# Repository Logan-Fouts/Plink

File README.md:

# Plink

**A low-cost, velocity-sensitive USB MIDI keyboard built on the Raspberry Pi Pico, using Hall-effect key switches.**

Plink reads 16 magnetic (Hall-effect) key switches through an analog multiplexer, works out how fast each key was pressed, and sends MIDI notes with velocity over USB. Each key has its own NeoPixel LED, and two front-panel buttons transpose the keyboard up or down.

> **Status:** early prototype (v1.0 hardware in progress). The firmware works on a breadboard build; the PCB and enclosure are still in progress.

---

## Features

- **Velocity-sensitive keys.** Velocity comes from how long a key takes to travel between two points in its stroke, read by an analog Hall sensor.
- **Plug-and-play USB MIDI.** The keyboard shows up as a USB composite device (MIDI + serial). It needs no drivers on Windows, macOS or Linux.
- **Automatic calibration.** Each key's resting value is measured at power-up, and its full-press value is learned as you play.
- **Per-key RGB feedback.** One WS2812 (NeoPixel) LED per key, driven by the RP2040's PIO.
- **Transpose.** ±24 semitones from two push buttons. Press both at once to reset.
- **Unit-tested input logic.** The input logic sits behind a small hardware abstraction layer, so it builds and runs its tests on a desktop machine.

## Hardware

### Bill of materials (v1.0)

| Part | Qty | Notes |
| --- | --- | --- |
| [Raspberry Pi Pico](https://www.raspberrypi.com/products/raspberry-pi-pico/) (RP2040) | 1 | Microcontroller + USB |
| [CD74HC4067](https://www.digikey.com/en/products/detail/texas-instruments/CD74HC4067SM96/390310) 16-channel analog mux | 1 | Feeds all key sensors into a single ADC pin |
| [Hall-effect linear switches](https://www.maxgaming.se/sv/switchar/moyu-studio-yurui-he-linear-switch) | 16 | Magnetic key switches |
| [SS49E linear Hall sensors](https://www.electrokit.com/en/ss49eua-to-92-hall-effektsensor-2mv/g) | 16 | One under each switch |
| [WS2812 NeoPixels](https://www.digikey.com/en/products/detail/adafruit-industries-llc/1655/5154679) | 16 | One per key |
| Momentary push buttons | 2 | Transpose down / up |

### Pinout

All pin assignments live in [`src/config.h`](src/config.h).

### Design files

- [`hardware/plink_kicad/`](hardware/plink_kicad): KiCad schematic, PCB and custom symbol/footprint libraries
- [`hardware/plink_freecad/`](hardware/plink_freecad): FreeCAD models of the case and components (switch, sensor, LEDs)

## Getting started

### Prerequisites

- [Pico SDK](https://github.com/raspberrypi/pico-sdk) (2.x) with the `PICO_SDK_PATH` environment variable set
- `arm-none-eabi-gcc` toolchain
- CMake ≥ 3.13 (≥ 3.20 for tests)
- A host C compiler (gcc/clang) for running the unit tests

### Clone

```bash
git clone --recurse-submodules https://github.com/Logan-Fouts/Plink.git
cd Plink
```

If you already cloned without `--recurse-submodules`, run `git submodule update --init` to fetch the Unity test framework.

### Build the firmware

```bash
cmake -S . -B build
cmake --build build
```

This produces `build/plink.uf2`.

> **`unrecognized command-line option '-mthumb'`?** CMake is using your desktop `gcc` instead of `arm-none-eabi-gcc`, usually because of a stale cache or an editor kit (for example VS Code CMake Tools set to "GCC x86_64"). Delete the cache and configure again: `rm -rf build/CMakeCache.txt build/CMakeFiles && cmake -S . -B build`.

### Flash

1. Hold **BOOTSEL** on the Pico and plug it into USB. It mounts as a drive named `RPI-RP2`.
2. Copy `build/plink.uf2` onto that drive. The Pico reboots into the firmware.

Or, with [picotool](https://github.com/raspberrypi/picotool):

```bash
picotool load -x build/plink.uf2 -f
```

### Play

Keep your hands off the keys while the keyboard powers up, because each key's resting value is calibrated at boot. After that, open any DAW or MIDI monitor and select the Plink MIDI device.

## Configuration

All tunable settings are compile-time constants in [`src/config.h`](src/config.h):

| Setting | Default | What it does |
| --- | --- | --- |
| `KEY_MAP` | ch 0–15 → notes 60–75 | Mux channel and base MIDI note for each key |
| `HALL_THRESHOLD_LOW` / `HIGH` | 200 / 700 | Travel points (‰) where velocity timing starts and the note fires |
| `HALL_THRESHOLD_RELEASE` | 150 | Travel below which a key counts as released |
| `VELOCITY_FAST_US` / `SLOW_US` | 2 ms / 60 ms | Travel times that map to velocity 127 / 1 |
| `MIDI_CHANNEL` | 0 | MIDI channel (0 = channel 1) |
| `LED_BRIGHTNESS` | 64 | Global LED brightness (0–255) |
| `TRANSPOSE_MIN` / `MAX` | −24 / +24 | Transpose range in semitones |
| `DEBUG` / `DEBUG_STREAM_KEY` | on / key 0 | Serial debug output and live sensor stream |

## Debugging

The keyboard also exposes a USB serial port. Open it with any terminal (`screen`, `minicom`, PuTTY, the VS Code Serial Monitor) to see key events, velocities and transpose changes. With `DEBUG_STREAM_KEY` set, one key's raw ADC value and position are printed every 20 ms, which helps when tuning thresholds.

## Running the tests

The input logic (mux reading, key state machine, push-button debouncing) is tested on the host with [Unity](https://github.com/ThrowTheSwitch/Unity):

```bash
cmake -S test -B build/test
cmake --build build/test
ctest --test-dir build/test --output-on-failure
```

## Code style

Code is formatted with **clang-format** and checked with **clang-tidy**. The tool versions are pinned in `requirements-dev.txt`.

```bash
python3 -m venv .venv && .venv/bin/pip install -r requirements-dev.txt   # one-time
scripts/install-hooks.sh     # one-time: auto-format staged files on every commit

scripts/format.sh            # format everything
scripts/lint.sh              # static analysis (needs a configured firmware build in build/)
```

CI checks formatting, runs the unit tests, builds the firmware and runs clang-tidy on every push and pull request. Tagging a version (`git tag v1.0.0 && git push --tags`) publishes a release with the `.uf2` attached.

## Project layout

```
Plink/
├── src/
│   ├── main.c            # Startup and main loop
│   ├── config.h          # Pins, thresholds and other tunables
│   ├── input/            # Keys, Hall-sensor state machine, mux, push buttons
│   ├── leds/             # NeoPixel buffer + WS2812 PIO program
│   ├── midi/             # USB MIDI output
│   ├── usb/              # TinyUSB config and descriptors
│   ├── debug/            # Serial debug printing
│   └── hardware/         # Hardware abstraction layer (RP2040 implementation)
├── test/                 # Host-side unit tests and hardware fakes
├── scripts/              # format.sh, lint.sh, git hooks
├── hardware/             # KiCad PCB + FreeCAD mechanical models
├── docs/                 # Developer documentation
└── lib/Unity/            # Unit-test framework (git submodule)
```

## Roadmap

- [x] Velocity-sensitive Hall-effect keys over USB MIDI
- [x] Per-key NeoPixel feedback
- [x] Transpose buttons
- [ ] Custom PCB (in progress)
- [ ] Enclosure
- [ ] Potentiometers / knobs sending MIDI CC
- [ ] MIDI input handling
- [ ] Generative, parameterised note patterns (second core)

## Documentation

For architecture, module internals and how to extend the firmware, see the **[Developer Guide](docs/DevDocs.md)**.

## License

No license has been chosen yet. Until one is added, all rights are reserved.

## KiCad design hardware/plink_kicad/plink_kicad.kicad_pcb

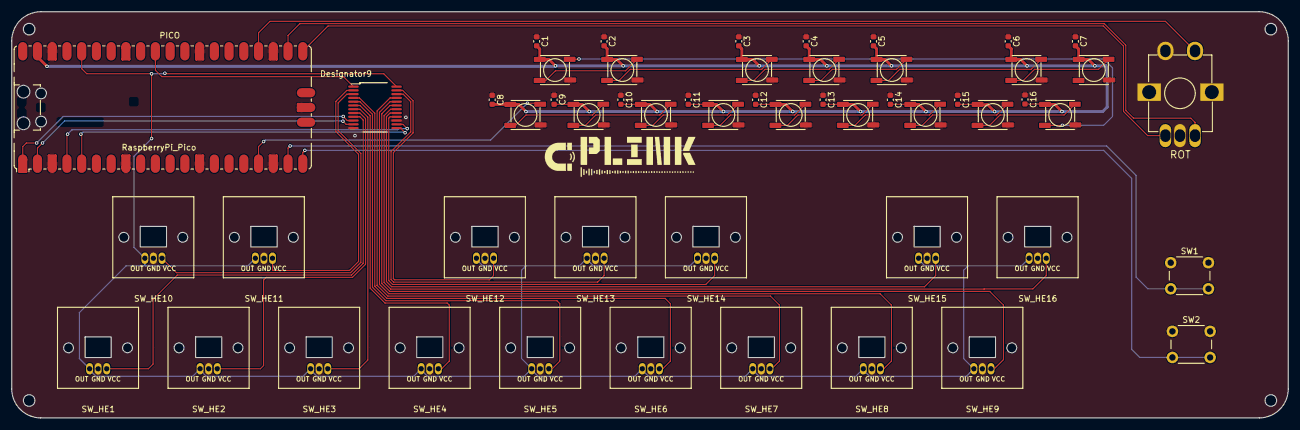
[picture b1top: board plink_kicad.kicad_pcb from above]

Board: 2 copper layers, 220.0 x 70.0 mm, 53 parts (0 on the bottom side), 45 nets.

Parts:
C1, C2, C3, C4, C5, C6, C7, C8, C9, C10, C11, C12, C13, C14, C15, C16: C; C_0603_1608Metric
LED1, LED2, LED3, LED4, LED5, LED6, LED7, LED8, LED9, LED10, LED11, LED12, LED13, LED14, LED15, LED16: SMD Neopixel 5050
PICO: RaspberryPi_Pico; RaspberryPi_Pico_SMD_HandSolder
ROT: Rotationsenkoder 1530 pv med tryckknapp
SW1, SW2: SW_Push; SW_PUSH_6mm
SW_HE1, SW_HE2, SW_HE3, SW_HE4, SW_HE5, SW_HE6, SW_HE7, SW_HE8, SW_HE9, SW_HE10, SW_HE11, SW_HE12, SW_HE13, SW_HE14, SW_HE15, SW_HE16: SW_Cherry_MX_1.00u_PCB_HALL_EFFECT; SW_Cherry_MX_HE_1.00u
U2: CD74HC4067SM96; DB0024A_M

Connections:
+3V: PICO.36 (3V3), SW_HE1.1 (VCC), SW_HE2.1 (VCC), SW_HE3.1 (VCC), SW_HE4.1 (VCC), SW_HE5.1 (VCC), SW_HE6.1 (VCC), SW_HE7.1 (VCC), SW_HE8.1 (VCC), SW_HE9.1 (VCC), SW_HE10.1 (VCC), SW_HE11.1 (VCC), SW_HE12.1 (VCC), SW_HE13.1 (VCC), SW_HE14.1 (VCC), SW_HE15.1 (VCC), SW_HE16.1 (VCC), U2.24 (VCC)
+5V: C1.2, C2.2, C3.2, C4.2, C5.2, C6.2, C7.2, C8.2, C9.2, C10.2, C11.2, C12.2, C13.2, C14.2, C15.2, C16.2, LED1.1 (VDD), LED2.1 (VDD), LED3.1 (VDD), LED4.1 (VDD), LED5.1 (VDD), LED6.1 (VDD), LED7.1 (VDD), LED8.1 (VDD), LED9.1 (VDD), LED10.1 (VDD), LED11.1 (VDD), LED12.1 (VDD), LED13.1 (VDD), LED14.1 (VDD), LED15.1 (VDD), LED16.1 (VDD), PICO.39 (VSYS)
CH0: SW_HE1.3 (OUT), U2.9 (I0)
CH1: SW_HE2.3 (OUT), U2.8 (I1)
CH2: SW_HE3.3 (OUT), U2.7 (I2)
CH3: SW_HE4.3 (OUT), U2.6 (I3)
CH4: SW_HE5.3 (OUT), U2.5 (I4)
CH5: SW_HE6.3 (OUT), U2.4 (I5)
CH6: SW_HE7.3 (OUT), U2.21 (I10)
CH7: SW_HE8.3 (OUT), U2.20 (I11)
CH8: SW_HE9.3 (OUT), U2.19 (I12)
CH9: SW_HE10.3 (OUT), U2.3 (I6)
CH10: SW_HE11.3 (OUT), U2.2 (I7)
CH11: SW_HE12.3 (OUT), U2.23 (I8)
CH12: SW_HE13.3 (OUT), U2.22 (I9)
CH13: SW_HE14.3 (OUT), U2.16 (I15)
CH14: SW_HE15.3 (OUT), U2.17 (I14)
CH15: SW_HE16.3 (OUT), U2.18 (I13)
GND: C1.1, C2.1, C3.1, C4.1, C5.1, C6.1, C7.1, C8.1, C9.1, C10.1, C11.1, C12.1, C13.1, C14.1, C15.1, C16.1, LED1.3 (VSS), LED2.3 (VSS), LED3.3 (VSS), LED4.3 (VSS), LED5.3 (VSS), LED6.3 (VSS), LED7.3 (VSS), LED8.3 (VSS), LED9.3 (VSS), LED10.3 (VSS), LED11.3 (VSS), LED12.3 (VSS), LED13.3 (VSS), LED14.3 (VSS), LED15.3 (VSS), LED16.3 (VSS), PICO.3 (GND), PICO.8 (GND), PICO.13 (GND), PICO.18 (GND), PICO.23 (GND), PICO.28 (GND), PICO.38 (GND), ROT.3 (C_COM), ROT.4 (D_SW), ROT.6 (MP), ROT.7 (MP), SW1.1, SW2.1, SW_HE1.2 (GND), SW_HE2.2 (GND), SW_HE3.2 (GND), SW_HE4.2 (GND), SW_HE5.2 (GND), SW_HE6.2 (GND), SW_HE7.2 (GND), SW_HE8.2 (GND), SW_HE9.2 (GND), SW_HE10.2 (GND), SW_HE11.2 (GND), SW_HE12.2 (GND), SW_HE13.2 (GND), SW_HE14.2 (GND), SW_HE15.2 (GND), SW_HE16.2 (GND), U2.12 (GND), U2.15 (E_N)
LED DIN: LED1.4 (DIN), PICO.17 (GPIO13)
unnamed: LED1.2 (DOUT), LED2.4 (DIN)
unnamed: LED2.2 (DOUT), LED3.4 (DIN)
unnamed: LED3.2 (DOUT), LED4.4 (DIN)
unnamed: LED4.2 (DOUT), LED5.4 (DIN)
unnamed: LED5.2 (DOUT), LED6.4 (DIN)
unnamed: LED6.2 (DOUT), LED7.4 (DIN)
unnamed: LED7.2 (DOUT), LED8.4 (DIN)
unnamed: LED8.2 (DOUT), LED9.4 (DIN)
unnamed: LED9.2 (DOUT), LED10.4 (DIN)
unnamed: LED10.2 (DOUT), LED11.4 (DIN)
unnamed: LED11.2 (DOUT), LED12.4 (DIN)
unnamed: LED12.2 (DOUT), LED13.4 (DIN)
unnamed: LED13.2 (DOUT), LED14.4 (DIN)
unnamed: LED14.2 (DOUT), LED15.4 (DIN)
unnamed: LED15.2 (DOUT), LED16.4 (DIN)
ROT A: PICO.21 (GPIO16), ROT.1 (A_OUT)
ROT B: PICO.22 (GPIO17), ROT.2 (B_OUT)
ROT SW: PICO.24 (GPIO18), ROT.5 (E_SW)
S0: PICO.1 (GPIO0), U2.10 (S0)
S1: PICO.2 (GPIO1), U2.11 (S1)
S2: PICO.4 (GPIO2), U2.14 (S2)
S3: PICO.5 (GPIO3), U2.13 (S3)
SIG: PICO.31 (GPIO26_ADC0), U2.1 (COMMON_I_O)
Shift Down: PICO.20 (GPIO15), SW2.2
Shift Up: PICO.19 (GPIO14), SW1.2

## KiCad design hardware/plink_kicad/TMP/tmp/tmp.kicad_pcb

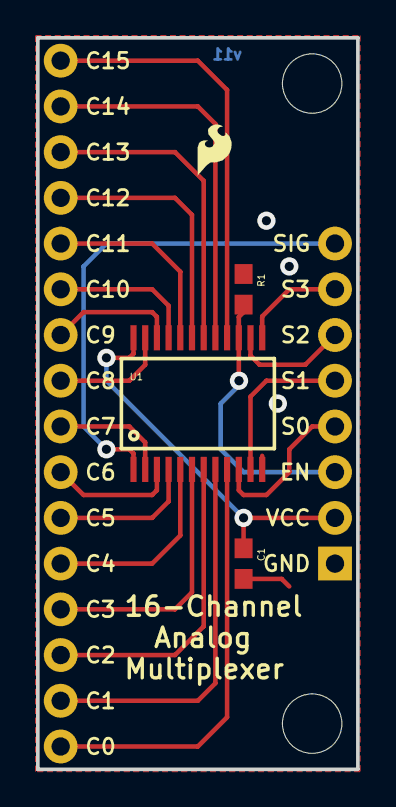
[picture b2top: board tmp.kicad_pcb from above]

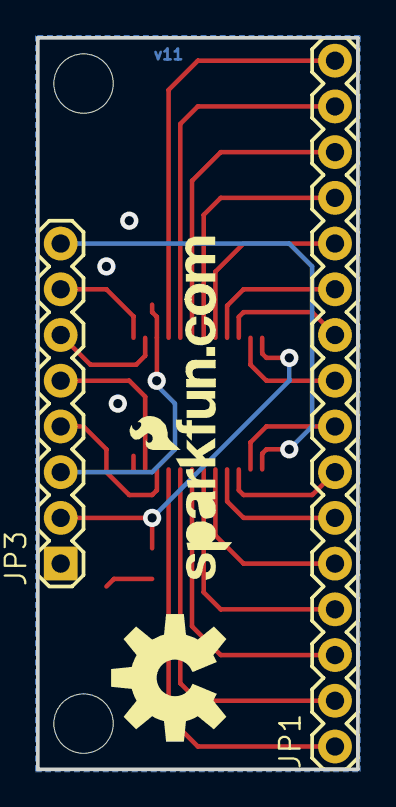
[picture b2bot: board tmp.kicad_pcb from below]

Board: 2 copper layers, 17.8 x 40.6 mm, 12 parts (4 on the bottom side), 24 nets.

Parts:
C1: 0.1uF; 0603
FRAME1: FRAME-LETTER; CREATIVE_COMMONS
JP1: 1X16
JP3: 1X08
LOGO1: OSHW-LOGOL; OSHW-LOGO-L
LOGO2: LOGO-SFESK; SFE-LOGO-FLAME
R1: 10K; 0603
STANDOFF1, STANDOFF2: STAND-OFF
U1: MUX-74HC4067; SSOP24
U$1: LOGO-SFENEW; SFE-NEW-WEBLOGO
U$2: REVISION

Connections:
C0: JP1.1, U1.9
C1: JP1.2, U1.8
C2: JP1.3, U1.7
C3: JP1.4, U1.6
C4: JP1.5, U1.5
C5: JP1.6, U1.4
C6: JP1.7, U1.3
C7: JP1.8, U1.2
C8: JP1.9, U1.23
C9: JP1.10, U1.22
C10: JP1.11, U1.21
C11: JP1.12, U1.20
C12: JP1.13, U1.19
C13: JP1.14, U1.18
C14: JP1.15, U1.17
C15: JP1.16, U1.16
EN: JP3.3, R1.2, U1.15
GND: C1.2, JP3.1, R1.1, U1.12
S0: JP3.4, U1.10
S1: JP3.5, U1.11
S2: JP3.6, U1.14
S3: JP3.7, U1.13
SIG: JP3.8, U1.1
VCC: C1.1, JP3.2, U1.24
